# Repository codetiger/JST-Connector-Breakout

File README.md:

Connectors

| Pins | Rows | Type  | Pitch  | Count 
|------|------|-------|--------|-------
| 6    | 1    | GH    | 1.25mm | 1
| 2    | 1    | XH    | 2.5mm  | 1
| 8    | 1    | GH    | 1.25mm | 1
| 5    | 1    | PH    | 2.0mm  | 1
| 3    | 1    | GH    | 1.25mm | 3
| 2    | 1    | PH    | 2.0mm  | 3
| 16   | 2    | SHD   | 1.0mm  | 2
| 2    | 1    | GH    | 1.25mm | 1
| 4    | 1    | PH    | 2.0mm  | 1

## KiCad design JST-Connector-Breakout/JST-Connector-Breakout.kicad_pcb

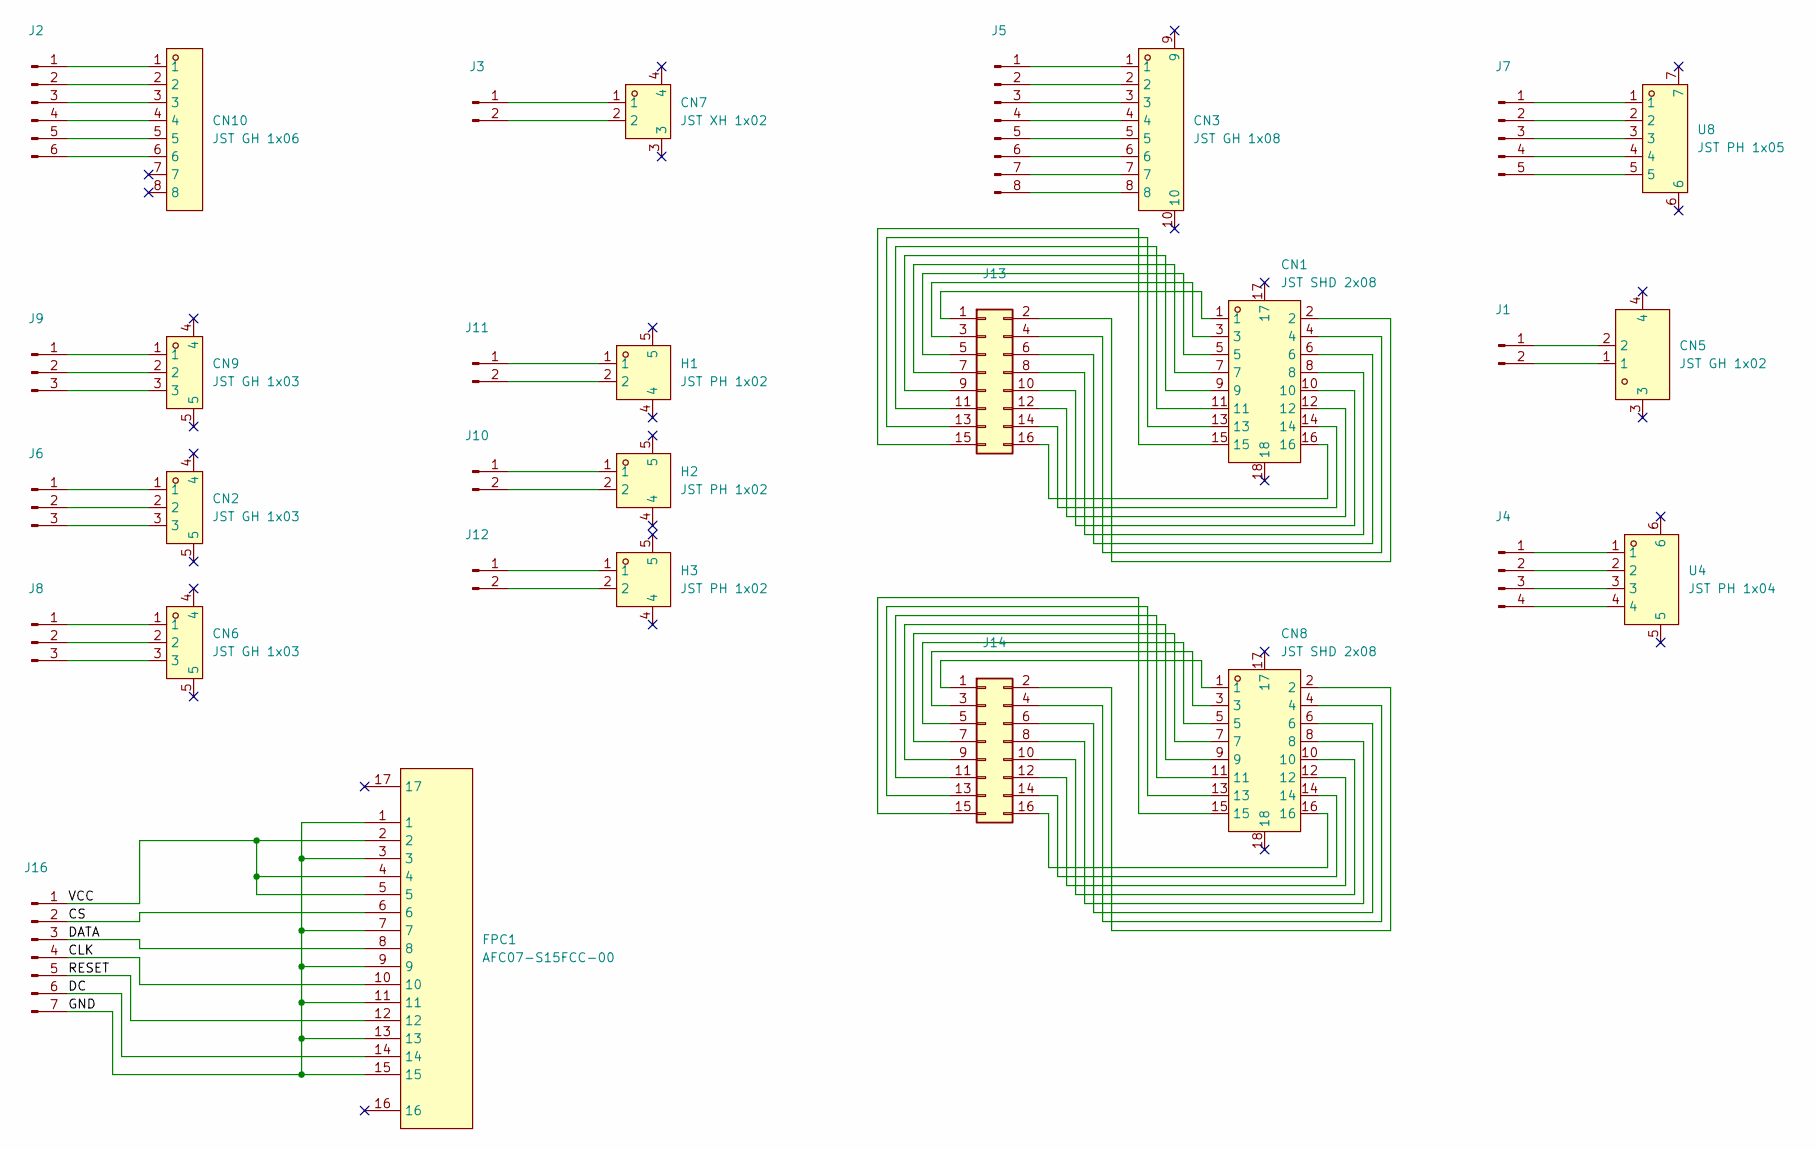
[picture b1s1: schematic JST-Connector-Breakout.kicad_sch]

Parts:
CN1, CN8: JST SHD 2x08; CONN-SMD_X1011WRS-2X08-9TV01; LCSC Part C718178
CN2, CN6, CN9: JST GH 1x03; CONN-SMD_HC-1.25-3PWT; LCSC Part C2845380
CN3: JST GH 1x08; CONN-SMD_8P-P1.25_YTC-A1251-08ABW; LCSC Part C7436577
CN5: JST GH 1x02; CONN-SMD_2P-P1.25-HC-1.25-2PWT; LCSC Part C2845379
CN7: JST XH 1x02; CONN-SMD_2P-P2.54-XH2.54-WT; LCSC Part C3029476
CN10: JST GH 1x06; CONN-SMD_6P-P1.25_HC-1.25-6PWT; Mfr. Part # HC-1.25-6PWT; LCSC Part C2845383
FPC1: AFC07-S15FCC-00; FPC-SMD_AFC07-S15FCC-00; LCSC Part C262209
H1, H2, H3: JST PH 1x02; CONN-SMD_2P-P2.00_XUNPU_WAFER-PH2.0-2PWB; LCSC Part C3029440
J1, J3, J10, J11, J12: Conn_01x02_Pin; PinHeader_1x02_P2.54mm_Vertical
J2: Conn_01x06_Pin; PinHeader_1x06_P2.54mm_Vertical
J4: Conn_01x04_Pin; PinHeader_1x04_P2.54mm_Vertical
J5: Conn_01x08_Pin; PinHeader_1x08_P2.54mm_Vertical
J6, J8, J9: Conn_01x03_Pin; PinHeader_1x03_P2.54mm_Vertical
J7: Conn_01x05_Pin; PinHeader_1x05_P2.54mm_Vertical
J13, J14: Conn_02x08_Odd_Even; PinHeader_2x08_P2.54mm_Vertical
J16: Conn_01x07_Pin; PinHeader_1x07_P2.54mm_Vertical
U4: JST PH 1x04; CONN-SMD_4P-P2.00_XUNPU_WAFER-PH2.0-4PWB; LCSC Part C3029442
U8: JST PH 1x05; CONN-SMD_5P-P2.00_XUNPU_WAFER-PH2.0-5PWB; LCSC Part C3029443

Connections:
/CLK: FPC1.10, J16.4
/CS: FPC1.6, J16.2
/DATA: FPC1.8, J16.3
/DC: FPC1.14, J16.6
/GND: FPC1.1, FPC1.3, FPC1.7, FPC1.9, FPC1.11, FPC1.13, FPC1.15, J16.7
/RESET: FPC1.12, J16.5
/VCC: FPC1.2, FPC1.4, FPC1.5, J16.1
unnamed: CN5.2, J1.1
unnamed: CN5.1, J1.2
unnamed: CN10.1, J2.1
unnamed: CN10.2, J2.2
unnamed: CN10.3, J2.3
unnamed: CN10.4, J2.4
unnamed: CN10.5, J2.5
unnamed: CN10.6, J2.6
unnamed: CN7.1, J3.1
unnamed: CN7.2, J3.2
unnamed: J4.1, U4.1
unnamed: J4.2, U4.2
unnamed: J4.3, U4.3
unnamed: J4.4, U4.4
unnamed: CN3.1, J5.1
unnamed: CN3.2, J5.2
unnamed: CN3.3, J5.3
unnamed: CN3.4, J5.4
unnamed: CN3.5, J5.5
unnamed: CN3.6, J5.6
unnamed: CN3.7, J5.7
unnamed: CN3.8, J5.8
unnamed: CN2.1, J6.1
unnamed: CN2.2, J6.2
unnamed: CN2.3, J6.3
unnamed: J7.1, U8.1
unnamed: J7.2, U8.2
unnamed: J7.3, U8.3
unnamed: J7.4, U8.4
unnamed: J7.5, U8.5
unnamed: CN6.1, J8.1
unnamed: CN6.2, J8.2
unnamed: CN6.3, J8.3
unnamed: CN9.1, J9.1
unnamed: CN9.2, J9.2
unnamed: CN9.3, J9.3
unnamed: H2.1, J10.1
unnamed: H2.2, J10.2
unnamed: H1.1, J11.1
unnamed: H1.2, J11.2
unnamed: H3.1, J12.1
unnamed: H3.2, J12.2
unnamed: CN1.1, J13.1
unnamed: CN1.2, J13.2
unnamed: CN1.3, J13.3
unnamed: CN1.4, J13.4
unnamed: CN1.5, J13.5
unnamed: CN1.6, J13.6
unnamed: CN1.7, J13.7
unnamed: CN1.8, J13.8
unnamed: CN1.9, J13.9
unnamed: CN1.10, J13.10
unnamed: CN1.11, J13.11
unnamed: CN1.12, J13.12
unnamed: CN1.13, J13.13
unnamed: CN1.14, J13.14
unnamed: CN1.15, J13.15
unnamed: CN1.16, J13.16
unnamed: CN8.1, J14.1
unnamed: CN8.2, J14.2
unnamed: CN8.3, J14.3
unnamed: CN8.4, J14.4
unnamed: CN8.5, J14.5
unnamed: CN8.6, J14.6
unnamed: CN8.7, J14.7
unnamed: CN8.8, J14.8
unnamed: CN8.9, J14.9
unnamed: CN8.10, J14.10
unnamed: CN8.11, J14.11
unnamed: CN8.12, J14.12
unnamed: CN8.13, J14.13
unnamed: CN8.14, J14.14
unnamed: CN8.15, J14.15
unnamed: CN8.16, J14.16

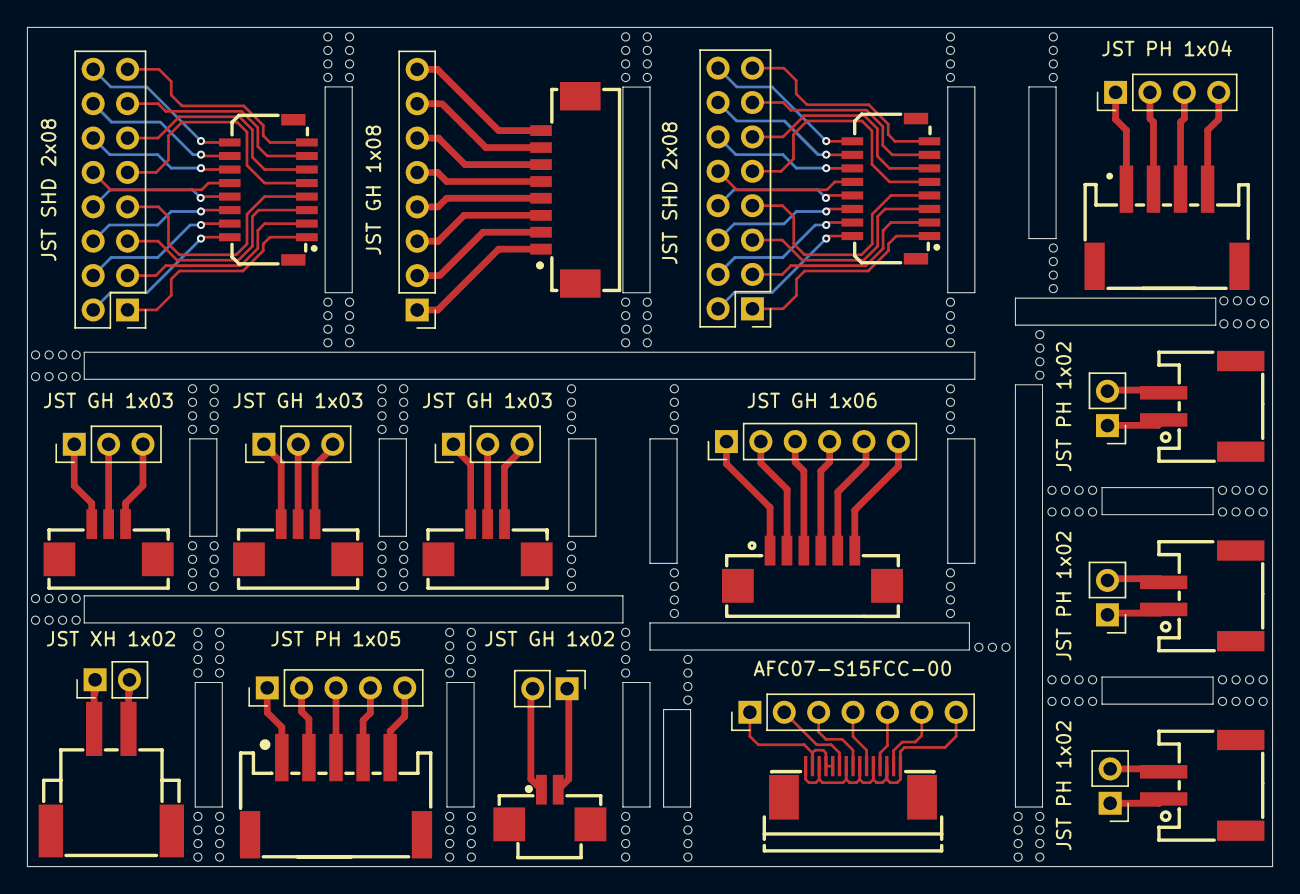
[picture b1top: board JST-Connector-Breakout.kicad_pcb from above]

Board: 2 copper layers, 92.0 x 62.0 mm, 30 parts (0 on the bottom side), 81 nets.

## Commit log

2024-07-29 PCB design ready for fab
2024-07-30 PCB panelizing with mouse bites
2026-06-25 Refine BOM and fabrication settings for JST breakout
    - Exclude non-fitted/connector parts from BOM (in_bom no)
    - Add Mfr. Part # for JST connector
    - Auto-place schematic net labels
    - Enable EXCLUDE DNP in fabrication toolkit
    - Regenerate production gerbers and add design backups
